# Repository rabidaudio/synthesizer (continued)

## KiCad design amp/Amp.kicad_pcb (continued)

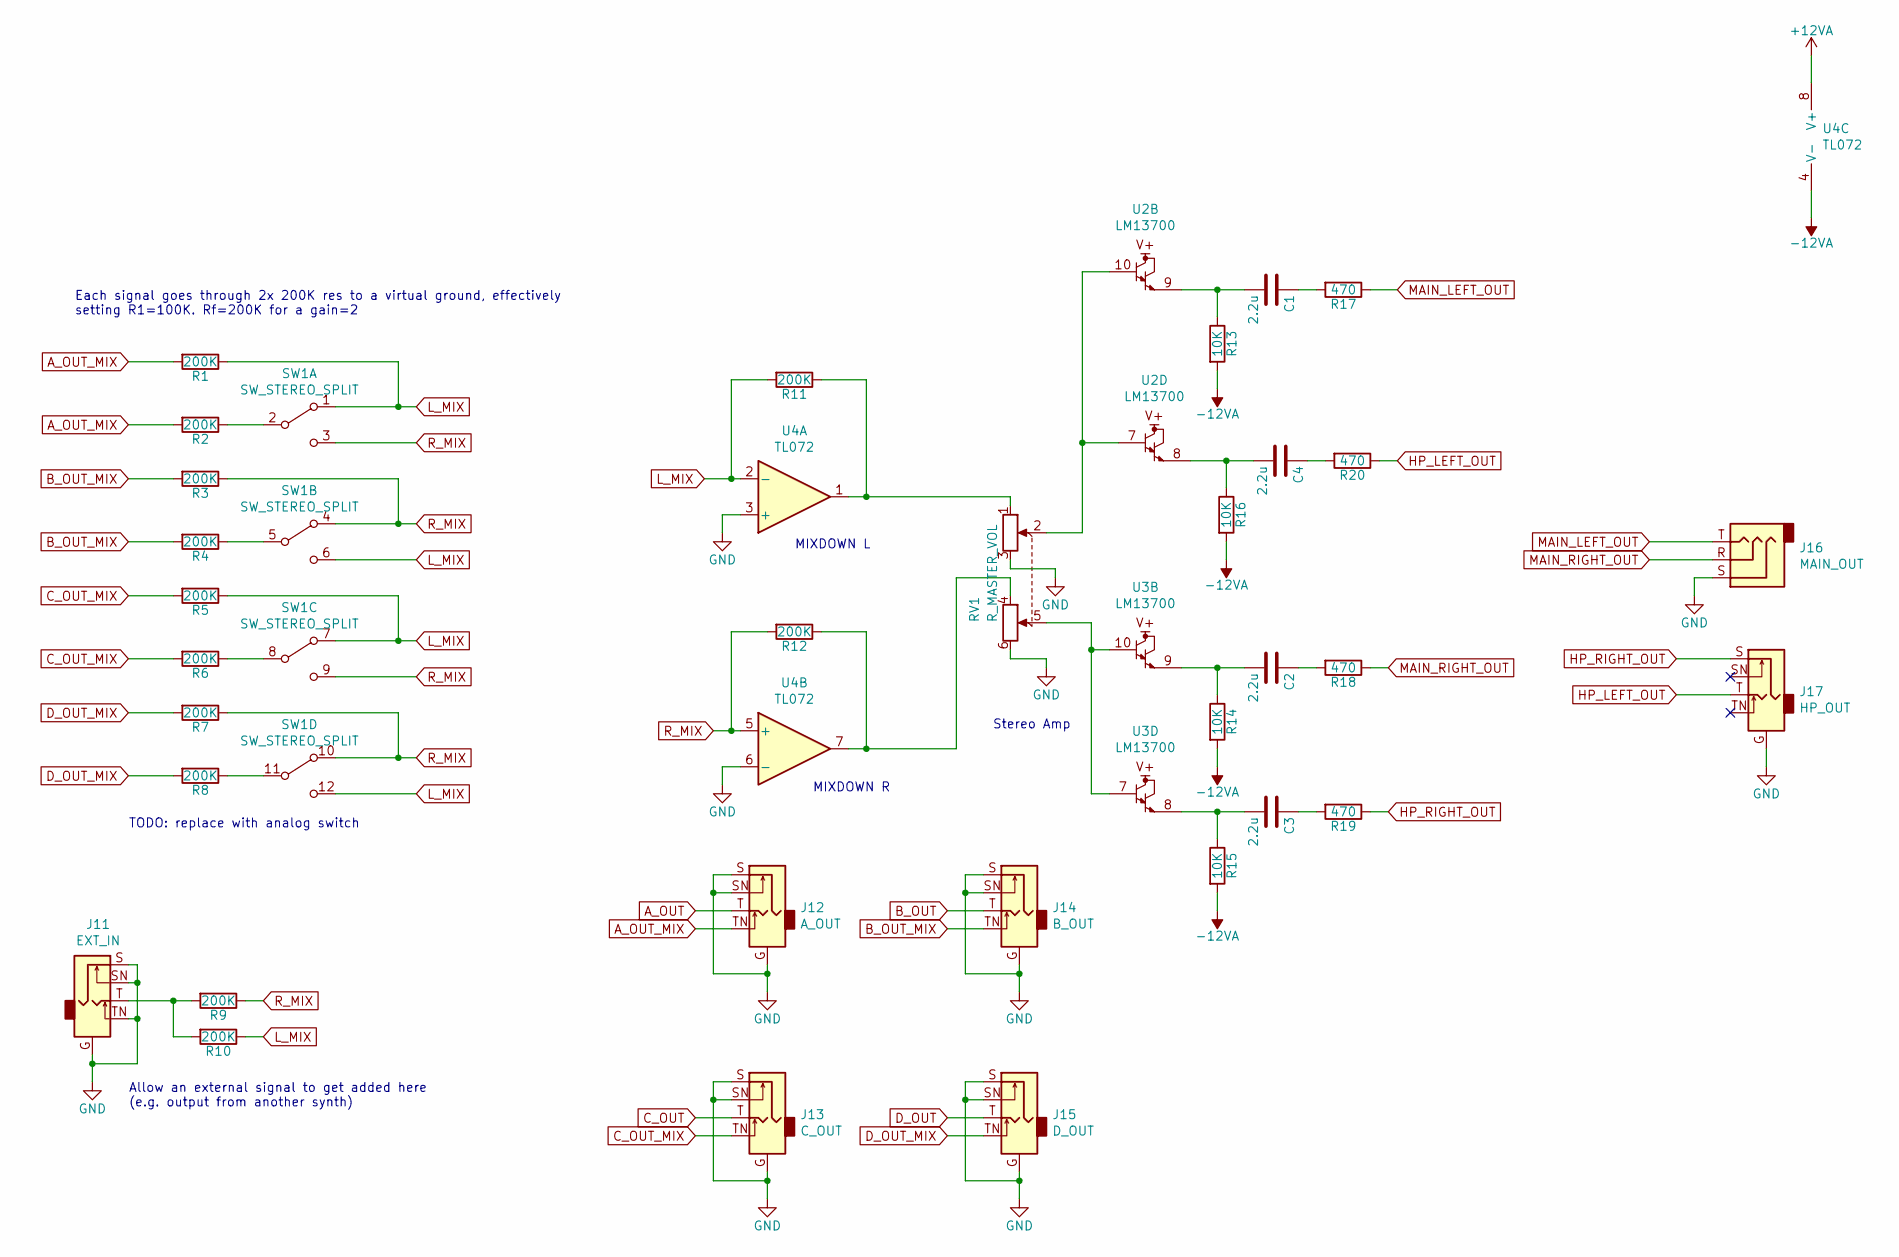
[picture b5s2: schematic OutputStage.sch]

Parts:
C1, C2, C3, C4: 2.2u; C_Radial_D6.3mm_H5.0mm_P2.50mm
J11: EXT_IN; 3.5MM_Jack_Breakout_Vertical
J12: A_OUT; 3.5MM_Jack_Breakout_Vertical
J13: C_OUT; 3.5MM_Jack_Breakout_Vertical
J14: B_OUT; 3.5MM_Jack_Breakout_Vertical
J15: D_OUT; 3.5MM_Jack_Breakout_Vertical
J16: MAIN_OUT; PinHeader_1x03_P2.54mm_Vertical
J17: HP_OUT; 3.5MM_Jack_Breakout_Vertical
R1, R2, R3, R4, R5, R6, R7, R8, R9, R10, R11, R12: 200K; R_Axial_DIN0204_L3.6mm_D1.6mm_P1.90mm_Vertical
R13, R14, R15, R16: 10K; R_Axial_DIN0204_L3.6mm_D1.6mm_P1.90mm_Vertical
R17, R18, R19, R20: 470; R_Axial_DIN0204_L3.6mm_D1.6mm_P1.90mm_Vertical
RV1: R_MASTER_VOL; PinHeader_2x03_P2.54mm_Vertical
SW1: SW_STEREO_SPLIT; PinHeader_2x06_P2.54mm_Vertical
U2, U3: LM13700; DIP-16_W7.62mm
U4: TL072; DIP-8_W7.62mm

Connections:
+12VA: U4.8 (V+); also elsewhere on the board
-12VA: R13.2, R14.2, R15.2, R16.2, U4.4 (V-); also elsewhere on the board
A_OUT: J12.T; also elsewhere on the board
A_OUT_MIX: J12.TN, R1.2, R2.2
B_OUT: J14.T; also elsewhere on the board
B_OUT_MIX: J14.TN, R3.2, R4.2
C_OUT: J13.T; also elsewhere on the board
C_OUT_MIX: J13.TN, R5.2, R6.2
D_OUT: J15.T; also elsewhere on the board
D_OUT_MIX: J15.TN, R7.2, R8.2
GND: J11.G, J11.S, J11.SN, J11.TN, J12.G, J12.S, J12.SN, J13.G, J13.S, J13.SN, J14.G, J14.S, J14.SN, J15.G, J15.S, J15.SN, J16.S, J17.G, RV1.3, RV1.6, U2.4 (-), U3.4 (-), U4.3 (+), U4.6 (-); also elsewhere on the board
HP_LEFT_OUT: J17.T, R20.1
HP_RIGHT_OUT: J17.S, R19.1
L_MIX: R1.1, R5.1, R10.1, R11.2, SW1.1 (A), SW1.6 (C), SW1.7 (A), SW1.12 (C), U4.2 (-)
MAIN_LEFT_OUT: J16.T, R17.1
MAIN_RIGHT_OUT: J16.R, R18.1
unnamed: C1.1, R17.2
unnamed: C1.2, R13.1, U2.9
unnamed: C2.1, R18.2
unnamed: C2.2, R14.1, U3.9
unnamed: C3.1, R19.2
unnamed: C3.2, R15.1, U3.8
unnamed: C4.1, R20.2
unnamed: C4.2, R16.1, U2.8
unnamed: J11.T, R9.2, R10.2
unnamed 60: U3.1; also elsewhere on the board
unnamed 63: U2.1; also elsewhere on the board
unnamed: R2.1, SW1.2 (B)
unnamed: R4.1, SW1.5 (B)
unnamed: R6.1, SW1.8 (B)
unnamed: R8.1, SW1.11 (B)
unnamed: R11.1, RV1.1, U4.1
unnamed: R12.1, RV1.4, U4.7
unnamed 91: U3.3 (+); also elsewhere on the board
unnamed 94: U3.5; also elsewhere on the board
unnamed 99: U2.3 (+); also elsewhere on the board
unnamed 102: U2.5; also elsewhere on the board
unnamed: RV1.2, U2.7, U2.10
unnamed: RV1.5, U3.7, U3.10
R_MIX: R3.1, R7.1, R9.1, R12.2, SW1.3 (C), SW1.4 (A), SW1.9 (C), SW1.10 (A), U4.5 (+)

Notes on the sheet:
Stereo Amp
Each signal goes through 2x 200K res to a virtual ground, effectively setting R1=100K. Rf=200K for a gain=2
MIXDOWN L
MIXDOWN R
Allow an external signal to get added here (e.g. output from another synth)
TODO: replace with analog switch

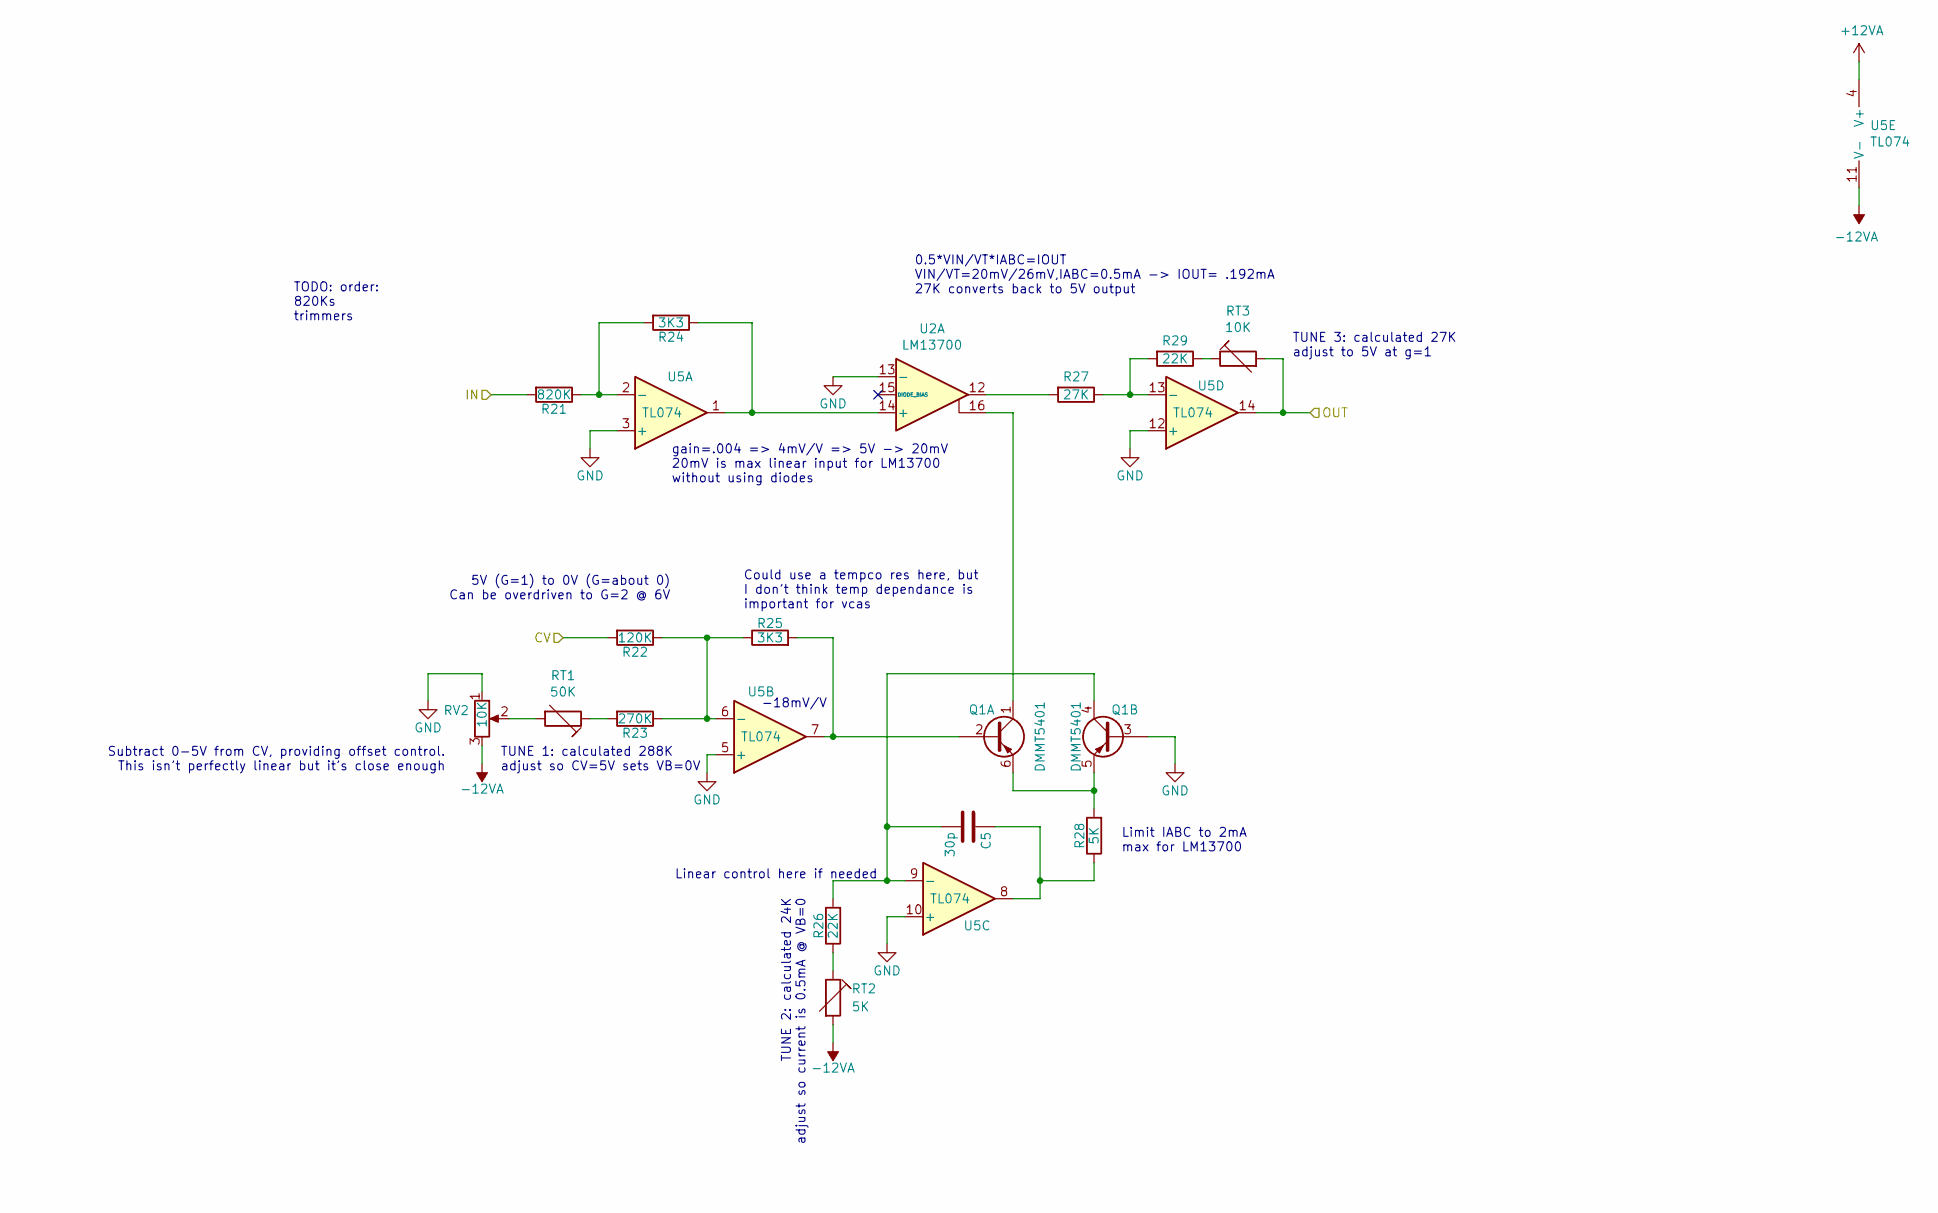
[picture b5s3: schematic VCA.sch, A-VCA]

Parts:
C5: 30p; C_Disc_D3.0mm_W2.0mm_P2.50mm
Q1: DMMT5401; SOT-23-6
R21: 820K; R_Axial_DIN0204_L3.6mm_D1.6mm_P1.90mm_Vertical
R22: 120K; R_Axial_DIN0204_L3.6mm_D1.6mm_P1.90mm_Vertical
R23: 270K; R_Axial_DIN0204_L3.6mm_D1.6mm_P1.90mm_Vertical
R24, R25: 3K3; R_Axial_DIN0204_L3.6mm_D1.6mm_P1.90mm_Vertical
R26, R29: 22K; R_Axial_DIN0204_L3.6mm_D1.6mm_P1.90mm_Vertical
R27: 27K; R_Axial_DIN0204_L3.6mm_D1.6mm_P1.90mm_Vertical
R28: 5K; R_Axial_DIN0204_L3.6mm_D1.6mm_P1.90mm_Vertical
RT1: 50K; R_Box_L14.0mm_W5.0mm_P9.00mm
RT2: 5K; R_Box_L14.0mm_W5.0mm_P9.00mm
RT3: 10K; R_Box_L14.0mm_W5.0mm_P9.00mm
RV2: 10K; slide_potentiometer_35mm
U2: LM13700; DIP-16_W7.62mm
U5: TL074; DIP-14_W7.62mm

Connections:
+12VA: U5.4 (V+); also elsewhere on the board
-12VA: RT2.2, RV2.3, U5.11 (V-); also elsewhere on the board
A_CV: R22.2; also elsewhere on the board
A_IN: R21.2; also elsewhere on the board
A_OUT: RT3.2, U5.14; also elsewhere on the board
GND: Q1.3 (B2), RV2.1, U2.4 (-), U2.13 (-), U5.3 (+), U5.5 (+), U5.10 (+), U5.12 (+); also elsewhere on the board
unnamed: C5.1, R28.1, U5.8
unnamed: C5.2, Q1.4 (C2), R26.2, U5.9 (-)
unnamed: Q1.1 (C1), U2.16
unnamed: Q1.2 (B1), R25.2, U5.7
unnamed: Q1.5 (E2), Q1.6 (E1), R28.2
unnamed 63: U2.1; also elsewhere on the board
unnamed: R21.1, R24.2, U5.2 (-)
unnamed: R22.1, R23.1, R25.1, U5.6 (-)
unnamed: R23.2, RT1.1
unnamed: R24.1, U2.14 (+), U5.1
unnamed: R26.1, RT2.1
unnamed: R27.1, R29.2, U5.13 (-)
unnamed: R27.2, U2.12
unnamed: R29.1, RT3.1
unnamed 99: U2.3 (+); also elsewhere on the board
unnamed 102: U2.5; also elsewhere on the board
unnamed: RT1.2, RV2.2

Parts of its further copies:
C6, C7, C8: 30p; C_Disc_D3.0mm_W2.0mm_P2.50mm
Q2, Q3, Q4: DMMT5401; SOT-23-6
R30, R39, R48: 820K; R_Axial_DIN0204_L3.6mm_D1.6mm_P1.90mm_Vertical
R31, R40, R49: 120K; R_Axial_DIN0204_L3.6mm_D1.6mm_P1.90mm_Vertical
R32, R41, R50: 270K; R_Axial_DIN0204_L3.6mm_D1.6mm_P1.90mm_Vertical
R33, R34, R42, R43, R51, R52: 3K3; R_Axial_DIN0204_L3.6mm_D1.6mm_P1.90mm_Vertical
R35, R38, R44, R47, R53, R56: 22K; R_Axial_DIN0204_L3.6mm_D1.6mm_P1.90mm_Vertical
R36, R45, R54: 27K; R_Axial_DIN0204_L3.6mm_D1.6mm_P1.90mm_Vertical
R37, R46, R55: 5K; R_Axial_DIN0204_L3.6mm_D1.6mm_P1.90mm_Vertical
RT4, RT7, RT10: 50K; R_Box_L14.0mm_W5.0mm_P9.00mm
RT5, RT8, RT11: 5K; R_Box_L14.0mm_W5.0mm_P9.00mm
RT6, RT9, RT12: 10K; R_Box_L14.0mm_W5.0mm_P9.00mm
RV3, RV4, RV5: 10K; slide_potentiometer_35mm
U6, U7, U8: TL074; DIP-14_W7.62mm

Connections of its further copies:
+12VA: U6.4 (V+), U7.4 (V+), U8.4 (V+); also elsewhere on the board
-12VA: RT5.2, RT8.2, RT11.2, RV3.3, RV4.3, RV5.3, U6.11 (V-), U7.11 (V-), U8.11 (V-); also elsewhere on the board
B_CV: R49.2; also elsewhere on the board
B_IN: R48.2; also elsewhere on the board
B_OUT: RT12.2, U8.14; also elsewhere on the board
C_CV: R31.2; also elsewhere on the board
C_IN: R30.2; also elsewhere on the board
C_OUT: RT6.2, U6.14; also elsewhere on the board
D_CV: R40.2; also elsewhere on the board
D_IN: R39.2; also elsewhere on the board
D_OUT: RT9.2, U7.14; also elsewhere on the board
GND: Q2.3 (B2), Q3.3 (B2), Q4.3 (B2), RV3.1, RV4.1, RV5.1, U6.3 (+), U6.5 (+), U6.10 (+), U6.12 (+), U7.3 (+), U7.5 (+), U7.10 (+), U7.12 (+), U8.3 (+), U8.5 (+), U8.10 (+), U8.12 (+); also elsewhere on the board
unnamed: C6.1, R37.1, U6.8
unnamed: C6.2, Q2.4 (C2), R35.2, U6.9 (-)
unnamed: C7.1, R46.1, U7.8
unnamed: C7.2, Q3.4 (C2), R44.2, U7.9 (-)
unnamed: C8.1, R55.1, U8.8
unnamed: C8.2, Q4.4 (C2), R53.2, U8.9 (-)
unnamed 57: Q2.1 (C1); also elsewhere on the board
unnamed: Q2.2 (B1), R34.2, U6.7
unnamed: Q2.5 (E2), Q2.6 (E1), R37.2
unnamed 60: Q3.1 (C1); also elsewhere on the board
unnamed: Q3.2 (B1), R43.2, U7.7
unnamed: Q3.5 (E2), Q3.6 (E1), R46.2
unnamed 63: Q4.1 (C1); also elsewhere on the board
unnamed: Q4.2 (B1), R52.2, U8.7
unnamed: Q4.5 (E2), Q4.6 (E1), R55.2
unnamed: R30.1, R33.2, U6.2 (-)
unnamed: R31.1, R32.1, R34.1, U6.6 (-)
unnamed: R32.2, RT4.1
unnamed 83: R33.1, U6.1; also elsewhere on the board
unnamed: R35.1, RT5.1
unnamed: R36.1, R38.2, U6.13 (-)
unnamed 86: R36.2; also elsewhere on the board
unnamed: R38.1, RT6.1
unnamed: R39.1, R42.2, U7.2 (-)
unnamed: R40.1, R41.1, R43.1, U7.6 (-)
unnamed: R41.2, RT7.1
unnamed 91: R42.1, U7.1; also elsewhere on the board
unnamed: R44.1, RT8.1
unnamed: R45.1, R47.2, U7.13 (-)
unnamed 94: R45.2; also elsewhere on the board
unnamed: R47.1, RT9.1
unnamed: R48.1, R51.2, U8.2 (-)
unnamed: R49.1, R50.1, R52.1, U8.6 (-)
unnamed: R50.2, RT10.1
unnamed 99: R51.1, U8.1; also elsewhere on the board
unnamed: R53.1, RT11.1
unnamed: R54.1, R56.2, U8.13 (-)
unnamed 102: R54.2; also elsewhere on the board
unnamed: R56.1, RT12.1
unnamed: RT4.2, RV3.2
unnamed: RT7.2, RV4.2
unnamed: RT10.2, RV5.2

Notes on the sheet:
5V (G=1) to 0V (G=about 0) Can be overdriven to G=2 @ 6V
Linear control here if needed
Subtract 0-5V from CV, providing offset control. This isn’t perfectly linear but it’s close enough
-18mV/V
TUNE 2: calculated 24K adjust so current is 0.5mA @ VB=0
Limit IABC to 2mA max for LM13700
gain=.004 => 4mV/V => 5V -> 20mV 20mV is max linear input for LM13700 without using diodes
0.5*VIN/VT*IABC=IOUT VIN/VT=20mV/26mV,IABC=0.5mA -> IOUT= .192mA 27K converts back to 5V output
TODO: order: 820Ks trimmers
Could use a tempco res here, but I don’t think temp dependance is important for vcas
TUNE 1: calculated 288K adjust so CV=5V sets VB=0V
TUNE 3: calculated 27K adjust to 5V at g=1

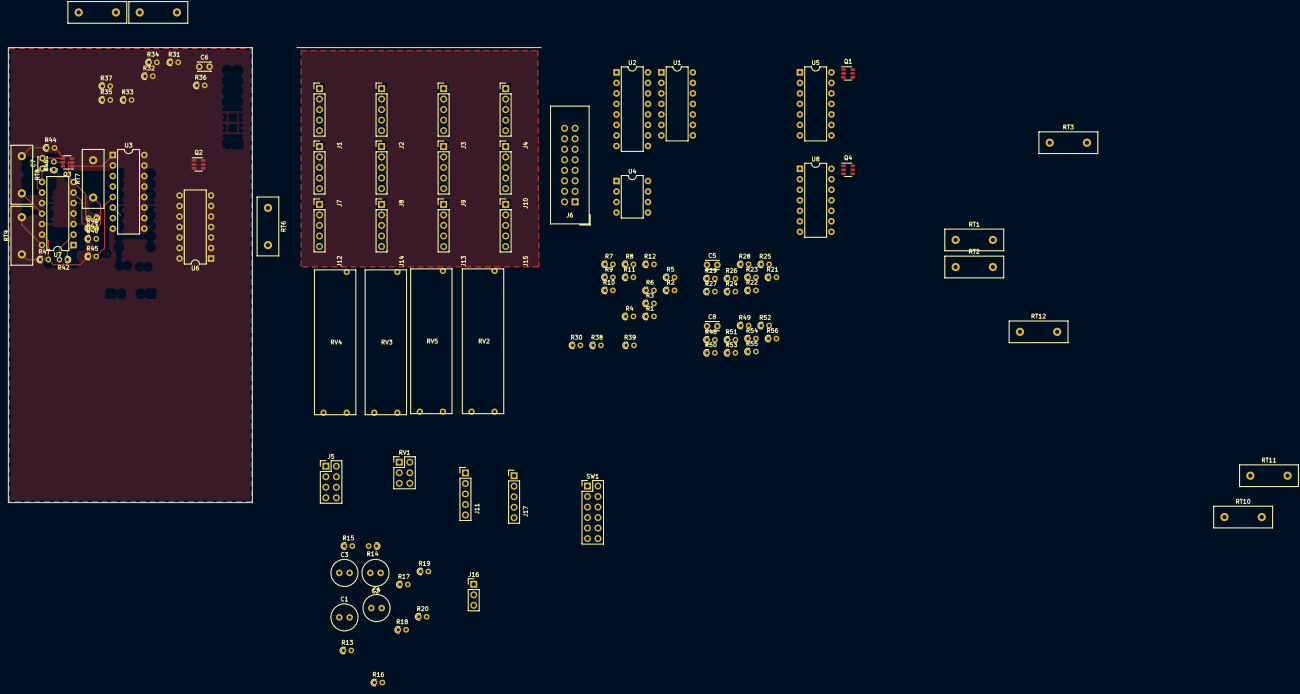
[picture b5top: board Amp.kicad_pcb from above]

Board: 2 copper layers, 128.8 x 110.0 mm, 111 parts (0 on the bottom side), 105 nets.

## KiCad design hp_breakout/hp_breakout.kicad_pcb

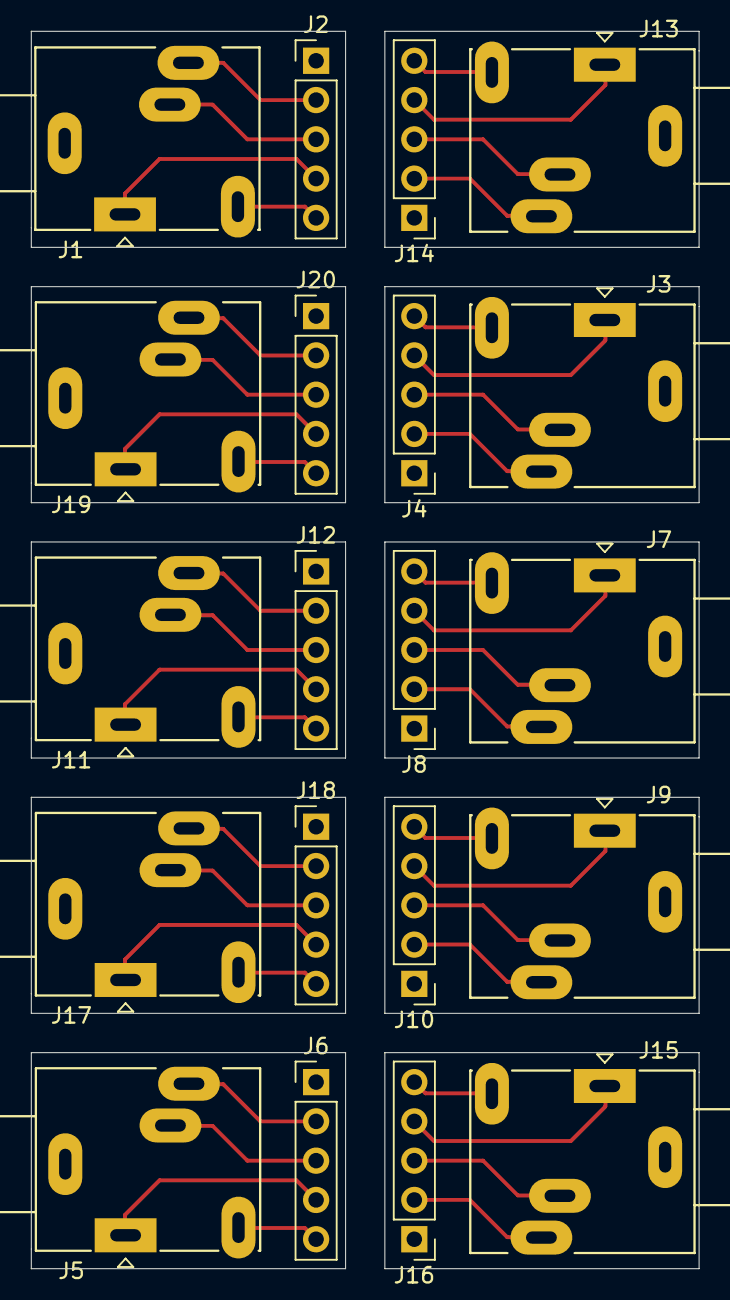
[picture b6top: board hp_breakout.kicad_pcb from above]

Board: 2 copper layers, 43.2 x 80.0 mm, 20 parts (0 on the bottom side), 50 nets.

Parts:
J1, J3, J5, J7, J9, J11, J13, J15, J17, J19: AudioJack2_Ground_Switch; Jack_3.5mm_Ledino_KB3SPRS_Horizontal
J2, J4, J6, J8, J10, J12, J14, J16, J18, J20: Conn_01x05_Male; PinHeader_1x05_P2.54mm_Vertical

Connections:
/U?/R: J1.R, J2.2
/U?/RN: J1.RN, J2.3
/U?/S: J1.S, J2.1
/U?/T: J1.T, J2.4
/U?/TN: J1.TN, J2.5
/sheet5E6F4A6A/R: J13.R, J14.2
/sheet5E6F4A6A/RN: J13.RN, J14.3
/sheet5E6F4A6A/S: J13.S, J14.1
/sheet5E6F4A6A/T: J13.T, J14.4
/sheet5E6F4A6A/TN: J13.TN, J14.5
/sheet5E6F4A6C/R: J15.R, J16.2
/sheet5E6F4A6C/RN: J15.RN, J16.3
/sheet5E6F4A6C/S: J15.S, J16.1
/sheet5E6F4A6C/T: J15.T, J16.4
/sheet5E6F4A6C/TN: J15.TN, J16.5
/sheet5E6F4A6E/R: J17.R, J18.2
/sheet5E6F4A6E/RN: J17.RN, J18.3
/sheet5E6F4A6E/S: J17.S, J18.1
/sheet5E6F4A6E/T: J17.T, J18.4
/sheet5E6F4A6E/TN: J17.TN, J18.5
/sheet5E6F4A68/R: J11.R, J12.2
/sheet5E6F4A68/RN: J11.RN, J12.3
/sheet5E6F4A68/S: J11.S, J12.1
/sheet5E6F4A68/T: J11.T, J12.4
/sheet5E6F4A68/TN: J11.TN, J12.5
/sheet5E6F4A70/R: J19.R, J20.2
/sheet5E6F4A70/RN: J19.RN, J20.3
/sheet5E6F4A70/S: J19.S, J20.1
/sheet5E6F4A70/T: J19.T, J20.4
/sheet5E6F4A70/TN: J19.TN, J20.5
/sheet5E6F46C9/R: J5.R, J6.2
/sheet5E6F46C9/RN: J5.RN, J6.3
/sheet5E6F46C9/S: J5.S, J6.1
/sheet5E6F46C9/T: J5.T, J6.4
/sheet5E6F46C9/TN: J5.TN, J6.5
/sheet5E6F46CB/R: J7.R, J8.2
/sheet5E6F46CB/RN: J7.RN, J8.3
/sheet5E6F46CB/S: J7.S, J8.1
/sheet5E6F46CB/T: J7.T, J8.4
/sheet5E6F46CB/TN: J7.TN, J8.5
/sheet5E6F47F3/R: J9.R, J10.2
/sheet5E6F47F3/RN: J9.RN, J10.3
/sheet5E6F47F3/S: J9.S, J10.1
/sheet5E6F47F3/T: J9.T, J10.4
/sheet5E6F47F3/TN: J9.TN, J10.5
/sheet5E6F4684/R: J3.R, J4.2
/sheet5E6F4684/RN: J3.RN, J4.3
/sheet5E6F4684/S: J3.S, J4.1
/sheet5E6F4684/T: J3.T, J4.4
/sheet5E6F4684/TN: J3.TN, J4.5

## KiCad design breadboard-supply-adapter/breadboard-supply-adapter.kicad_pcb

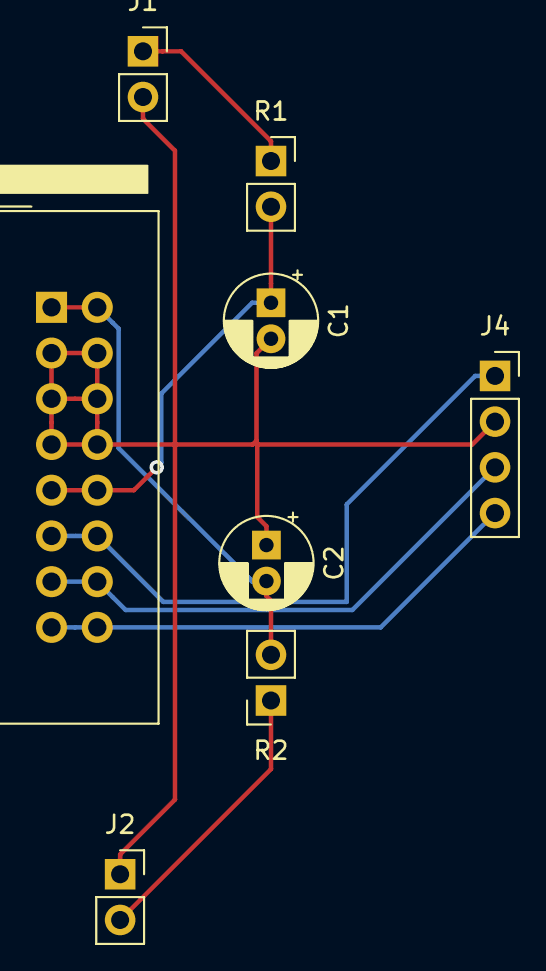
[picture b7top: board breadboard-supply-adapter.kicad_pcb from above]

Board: 2 copper layers, 8 parts (0 on the bottom side), 8 nets.

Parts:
C1, C2: CP; CP_Radial_D5.0mm_P2.00mm
J1, J2: Conn_01x02; PinSocket_1x02_P2.54mm_Vertical
J3: EURORACK_CONN_16_GATE_CV; EURORACK_16_IDC
J4: Conn_01x04; PinSocket_1x04_P2.54mm_Vertical
R1, R2: 0.5; PinSocket_1x02_P2.54mm_Vertical

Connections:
+12V: C1.1, J3.9, R1.2
-12V: C2.2, J3.1, R2.2
GND: C1.2, C2.1, J1.2, J2.1, J3.3, J4.2
unnamed: J1.1, R1.1
unnamed: J2.2, R2.1
unnamed: J3.11, J4.1
unnamed: J3.13, J4.3
unnamed: J3.15, J4.4

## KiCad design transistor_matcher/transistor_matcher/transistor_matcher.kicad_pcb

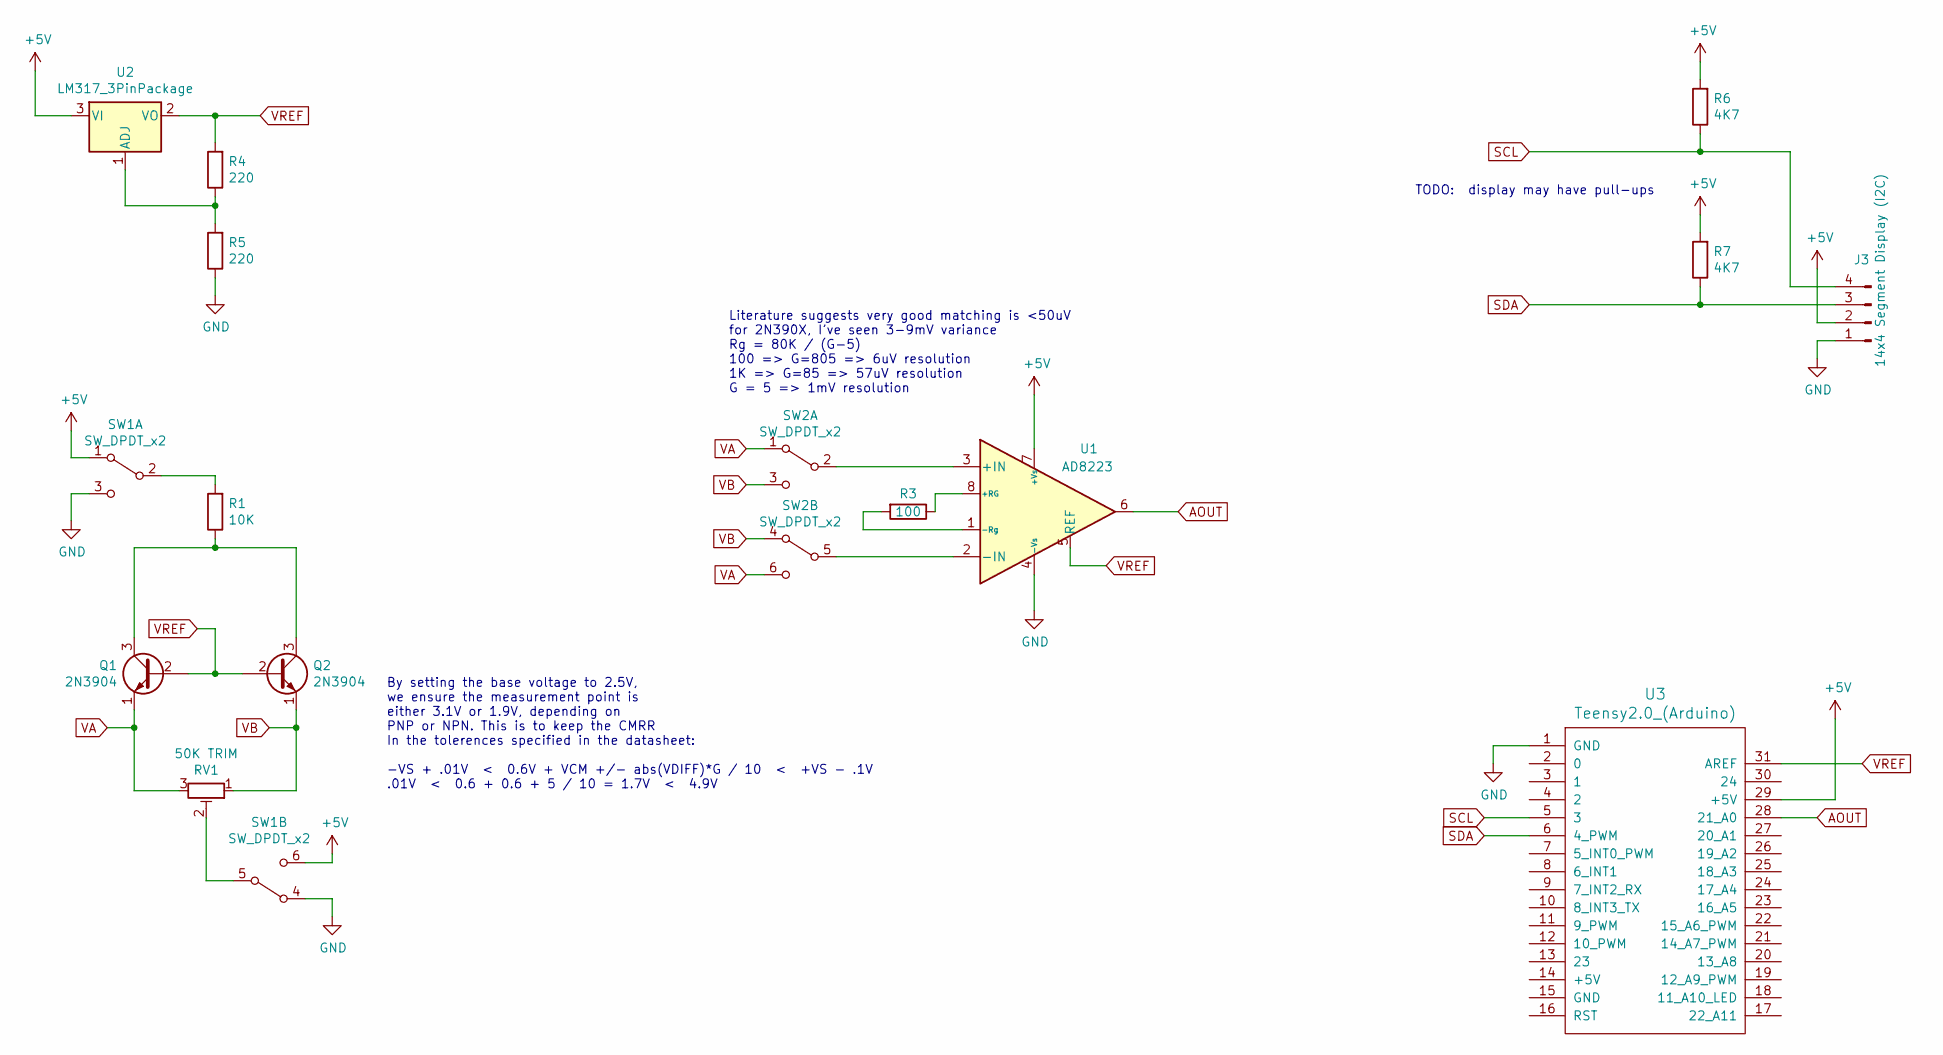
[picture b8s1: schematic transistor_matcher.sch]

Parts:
J3: 14x4 Segment Display (I2C); JST-4-PTH-VERT
Q1, Q2: 2N3904; BJT_Slot
R1: 10K; R_Axial_DIN0204_L3.6mm_D1.6mm_P1.90mm_Vertical
R3: 100; R_Axial_DIN0204_L3.6mm_D1.6mm_P1.90mm_Vertical
R4, R5: 220; R_Axial_DIN0204_L3.6mm_D1.6mm_P1.90mm_Vertical
R6, R7: 4K7; R_Axial_DIN0204_L3.6mm_D1.6mm_P1.90mm_Vertical
RV1: 50K TRIM; Potentiometer_Trimmer_Bourns_PV36W
SW1, SW2: SW_DPDT_x2; SW_E-Switch_EG1271_DPDT
U1: AD8223; SOIC-8_3.9x4.9mm_Pitch1.27mm
U2: LM317_3PinPackage; TO-220-3_Horizontal
U3: Teensy2.0_(Arduino); Teensy2.0

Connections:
+5V: J3.2, R6.2, R7.2, SW1.1 (A), SW1.6 (C), U1.7 (+Vs), U2.3 (VI), U3.29 (+5V)
AOUT: U1.6, U3.28 (21_A0)
GND: J3.1, R5.1, SW1.3 (C), SW1.4 (A), U1.4 (-Vs), U3.1 (GND)
unnamed: Q1.3 (C), Q2.3 (C), R1.1
unnamed: R1.2, SW1.2 (B)
unnamed: R3.1, U1.8 (+RG)
unnamed: R3.2, U1.1 (-Rg)
unnamed: R4.1, R5.2, U2.1 (ADJ)
unnamed: RV1.2, SW1.5 (B)
unnamed: SW2.2 (B), U1.3 (+IN)
unnamed: SW2.5 (B), U1.2 (-IN)
SCL: J3.4, R6.1, U3.5 (3)
SDA: J3.3, R7.1, U3.6 (4_PWM)
VA: Q1.1 (E), RV1.3, SW2.1 (A), SW2.6 (C)
VB: Q2.1 (E), RV1.1, SW2.3 (C), SW2.4 (A)
VREF: Q1.2 (B), Q2.2 (B), R4.2, U1.5 (REF), U2.2 (VO), U3.31 (AREF)

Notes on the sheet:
Literature suggests very good matching is <50uV for 2N390X, I’ve seen 3-9mV variance Rg = 80K / (G-5) 100 => G=805 => 6uV resolution 1K => G=85 => 57uV resolution G = 5 => 1mV resolution
By setting the base voltage to 2.5V, we ensure the measurement point is either 3.1V or 1.9V, depending on PNP or NPN. This is to keep the CMRR In the tolerences specified in the datasheet: -VS + .01V < 0.6V + VCM +/- abs(VDIFF)*G / 10 < +VS - .1V .01V < 0.6 + 0.6 + 5 / 10 = 1.7V < 4.9V
TODO: display may have pull-ups

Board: 2 copper layers, 15 parts (4 on the bottom side), 16 nets, no tracks yet.

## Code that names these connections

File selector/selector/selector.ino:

/** Configuration **/
// which pin to read from
const int analogPin = A1;
// number of bins
const int binCount = 4;
// which digital output pins to use for each bin
const int binPins[binCount] = { 0, 1, 3, 4 };
// the percent beyond the cutoff you must turn for a change to occur
const float hysteresis = 0.05;
#define DEBUG false

// it would be more efficient to use ints instead of floats but
// performance isn't really a concern here and it means we can
// easily support arbitrary configurations
const float binSize = 1024 / (float) binCount;
const float overlap = hysteresis * binSize;
size_t state = -1;

void setup() {
  for (size_t i = 0; i < binCount; i++) {
    pinMode(binPins[i], OUTPUT);
    digitalWrite(binPins[i], LOW);
  }
//  if (DEBUG) {
//    Serial.begin(9600);
//    Serial.print("binSize: "); Serial.println(binSize);
//    Serial.print("overlap: "); Serial.println(overlap);
//  }
}

void loop() {
  float value = (float) analogRead(analogPin);
//    if (DEBUG) {
//      Serial.print("value: "); Serial.println(value);
//    }
  float upperBound = ((state + 1) * binSize) + overlap;
  float lowerBound = (state * binSize) - overlap;
  if (value > upperBound) {
    setState(state + 1);
  } else if (value < lowerBound) {
    setState(state - 1);
  }
}

void setState(size_t s) {
  if (s == state) return;
  digitalWrite(binPins[state], LOW);
  digitalWrite(binPins[s], HIGH);
  state = s;
//  if (DEBUG) {
//    Serial.print("state: "); Serial.println(state);
//  }
}

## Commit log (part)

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2015-04-28 inital commit
2015-05-04 new stuff
2015-05-05 cleaned up
2015-05-05 added classwork
2015-05-05 added textbook
2015-05-05 added ADC, cleaned up schematic
2015-05-05 added osc for seq
2015-05-13 uncommited board changes
2015-05-15 started preso work
2015-05-17 the new sequencer kicks so much ass
2015-05-17 better comments
2015-05-17 updated sequencer eagle files for current version
2015-05-17 updated schematic for BOM
2015-05-20 board tweaks
2015-05-20 added pdf rendering stuff
2015-05-20 basic webcam stuff
2015-05-20 uggh i should have started this hours ago
2015-05-20 uggh
2015-05-20 fuck me
2015-05-20 might just make it
2015-05-20 fuckitshipit
2015-05-20 fingers crossed
2016-07-17 added other files
2019-04-11 started amplifier design
2019-04-15 getting close on the amp
2019-05-28 updated amp - LM13700 with PNP-exp. control
2020-03-15 created base connector breakout project
2020-03-15 10 identical boards
2020-03-15 update amp to kicad 5
2020-03-16 updated amp schematic with glue
2020-03-17 updated VCA based on new calculations
2020-03-17 added notes
2020-03-20 started transistor_matcher circuit
2020-03-20 updated schematic for VBE measurement, started on board layout
2020-03-21 simplfied based on emperical tests
2020-03-28 basic sketch to prove inst. amp is working I think we really need a constant upper reference voltage
2020-03-29 updated to include display
2020-04-05 got working amplifier
2020-04-05 separated amp into sheets
2020-05-03 updated notes
2020-05-20 reworked amp sheets and notes
2020-05-20 update amp config for quad-cascade design
2020-05-20 add eurorack connector, fix some issues
2020-05-21 initial vco notes (not thoroughly validated or calculated
2020-05-21 ltspice sim for lm13700 square/triangle vco
2020-05-23 rename shared kicad dir
2020-05-23 created utility module
2020-05-23 fix for eurorack connector
2020-05-23 added a few more untility footprints
2020-05-24 use jacks directly for horizontal
2020-05-24 switched fet with cd4066
2020-05-24 pcb mostly laid out
2020-05-24 cleanup
2020-05-24 shrunk board
2020-05-24 move the quirks of the pcb out of the schematic
2020-05-24 switch to 10-pin header
2020-05-24 use +/-10V power supply for amps
2020-05-24 reconnect 4066 headers
2020-05-25 LED driver for gate
2020-05-25 experimented some more with the led
2020-05-25 quick prototype of a breadboard power supply connector
2020-05-25 reversed the polarity of the neg cap (oops)
2020-05-28 rework PCB
2020-05-28 shrunk board significantly
2020-05-28 use through-holes for pot
2020-05-30 cleanup repo
2020-05-30 planning pannel layout
2020-05-30 testing 555 as pwm control
2020-05-30 add support for fixed CV output when no input
2020-05-30 correction based on breadboard test
2020-05-31 lots of panel design work
2020-05-31 correct ground issue
2020-05-31 move duplicate directory
2020-06-01 made progress on VCO
2020-06-02 fix some bugs in the circuit
2020-06-02 update graphics based on measurements
2020-06-02 fix amp connector
2020-06-06 it oscilates!
2020-06-06 vco planning
2020-06-06 output selector CV
2020-06-07 started vac layout
2020-06-07 more vca layout
2020-06-08 update amp
2020-06-08 working spice simulation
2020-06-08 added calculations
2020-06-08 adjust params to lower gain=1 current to keep shape up to gain=2
2020-06-08 updated schematic to match
2020-06-08 documented amplifier
2020-06-09 documented utils
2020-06-16 updated vco calculations
2020-06-16 experimenting with error
2020-06-17 add notes from test assembly
2020-07-04 reworked utilities around better analog switch modules
2020-07-04 restarted pcb
2020-07-04 reworked silkscreen
2020-07-04 corrected pin order on the pot breakout
2020-07-05 update components
2020-07-20 started envelope design
2020-07-20 tested utils rev b
2020-08-01 got analog latch working, started schematic
2020-08-01 component selection
2020-08-01 prepared pcb for dual envelopes
2020-08-01 cleanup amp
2020-08-01 clean up documentation
2020-08-01 fix indents
2020-08-02 remove outdated notes
2020-08-02 get rid of propigating controls
2020-08-02 adjusted amp to a 10V control voltage range
2020-08-02 scaled adsr to support 0-10V input
2020-08-02 use a current mirror to isolate reference currents, buffer vin, tune params
2020-08-02 use diode to force positive VIN
2020-08-02 update notes
2020-08-02 more accurate notes about lm13700
2020-08-02 notes
2020-08-03 add max simulation of transfer functions
2020-08-29 corrections based on prototype pcb
2020-08-31 output stage
2020-09-08 vco adjustments
2020-09-12 adjust waveshaper for 12V
2020-09-12 assembled breadboard VCO and waveshaper
2020-09-13 midi poc
2020-12-31 Update README.md
    add note about arp
2021-01-02 unsaved midi changes
2021-01-02 vco notes
2021-01-03 write code for shape selector, design CV input stage of vco
2021-07-07 trying 555 as square wave converter of osc core
2021-09-07 util tweaks
2021-09-11 add vactrol datasheets
2021-09-13 rework ASDR
2021-09-14 more layout
2021-09-14 reduce to one input
2021-09-21 layout
2022-02-06 adsr improvements
2022-09-10 planning and proof-of-concept code
2022-09-10 set up platformio
2022-09-10 refactor code
2022-09-11 switch to attiny84 and think more about control scheme
2022-09-12 add swing support
2022-09-14 basic control mechanism
2022-09-14 improve display
2022-09-14 implement tap tempo
2022-09-15 convert pot to rotary switch
2022-09-15 connect interface to rotary switch
2022-09-19 move reference to blog
2022-09-24 rework clock circuit
2022-09-24 proof-of-concept LED driver
2022-09-24 re-integrate new display with main code
2022-09-25 pcb layout first pass
2022-09-25 cleanup pcb and silkscreen
2022-10-08 additional cleanup
2022-10-08 switch to frequency correct mode and update bpm register values
2022-10-08 CV tempo control
2022-10-08 analog input pin protection
2022-10-16 refactor
2022-10-16 tuned
2022-10-16 reimport backpack code and make def switch for it
2022-10-16 set up code for bare uno option
2022-10-16 get working on bare mcu
2022-10-17 update pcb
2022-10-17 switch side of bottom header for structural support
2022-10-17 simplify some complex routing
2022-11-25 redesign pcb around rotary encoder
2022-11-25 make a bit more space
2023-01-01 testing rotary encoder
2023-01-01 working encoder
2023-01-01 verified hardware
2023-01-01 fix PCB
2023-01-01 beautify schematic
2023-01-02 update to Kicad 6 and fix some layout issues
2023-01-02 update adsr to kicad 6
2023-01-02 re-annotate schematic
2023-01-08 create panel for clock module
2023-01-21 fix 7-segment displays
2023-01-21 fix some PCB bugs
2023-01-21 fix inputs
2023-01-22 pause support
2023-01-31 re-create panel in kicad
2023-02-03 graphics
2023-02-14 updated layout
2023-02-20 updated panel
2023-02-27 new spooky designs
2023-02-27 test out on pcb
2023-03-05 import panel designs and assets
2023-03-05 updated component appearances
2023-03-05 minor adjustments for component bounds
2023-03-05 import alternate design
2023-03-06 make ground plane connected, move LEDs wide
2023-03-06 back graphics
2023-03-07 rendered main design
2023-03-07 added panel to pcb
2023-03-07 render alternate design
2023-03-07 render gerbers
2023-03-18 move logos to soldermask
2023-03-18 fix design issues
2023-03-18 subdivisions both ways
2023-03-18 flip display direction of subdivisions
2023-03-19 add support for saving and loading settings
2023-03-19 display the base value when changing, else true value
2023-03-19 refactor displays to abstract class
2023-04-30 fix swing
2023-04-30 adust resolution of swing to be in %
2023-04-30 rework menu setup
2023-04-30 fix bug in timer
2023-04-30 expand range
2023-04-30 cleanup readme
2023-05-01 increase crystal footprint
2023-05-01 generate rev b gerbers
2023-05-01 cleanup old files
2023-05-01 fixed and separated pcb
2024-10-22 add reusable openscad layout definitions
2024-10-22 create script for extracting center points from openscad dxf
2024-10-23 cleanup synth shared footprints
2024-10-23 flip y orientation
2024-10-23 reverse y-axis orientation
2024-10-23 Revert "reverse y-axis orientation"
    This reverts commit be2b3902423d8e89fe58d89905e9280b5649029d.
2024-10-23 Revert "flip y orientation"
    This reverts commit a8479f8d3d33ab95d629eb13d20a0d69ed88b72e.
2024-10-23 add reverse flag
2024-11-24 keepouts and courtyards for screw components
2024-11-24 fix keepouts
2025-12-01 Bump fonttools from 4.54.1 to 4.61.0 in /shared/extract_dxf_centers
    Bumps [fonttools](https://github.com/fonttools/fonttools) from 4.54.1 to 4.61.0.
    - [Release notes](https://github.com/fonttools/fonttools/releases)
    - [Changelog](https://github.com/fonttools/fonttools/blob/main/NEWS.rst)
    - [Commits](https://github.com/fonttools/fonttools/compare/4.54.1...4.61.0)
    ---
    updated-dependencies:
2025-12-16 Bump filelock from 3.16.1 to 3.20.1 in /shared/extract_dxf_centers
    Bumps [filelock](https://github.com/tox-dev/py-filelock) from 3.16.1 to 3.20.1.
    - [Release notes](https://github.com/tox-dev/py-filelock/releases)
    - [Changelog](https://github.com/tox-dev/filelock/blob/main/docs/changelog.rst)
    - [Commits](https://github.com/tox-dev/py-filelock/compare/3.16.1...3.20.1)
    ---
    updated-dependencies:
2026-01-13 Bump virtualenv from 20.27.0 to 20.36.1 in /shared/extract_dxf_centers
    Bumps [virtualenv](https://github.com/pypa/virtualenv) from 20.27.0 to 20.36.1.
    - [Release notes](https://github.com/pypa/virtualenv/releases)
    - [Changelog](https://github.com/pypa/virtualenv/blob/main/docs/changelog.rst)
    - [Commits](https://github.com/pypa/virtualenv/compare/20.27.0...20.36.1)
    ---
    updated-dependencies:
2026-01-13 Bump filelock from 3.16.1 to 3.20.3 in /shared/extract_dxf_centers
    Bumps [filelock](https://github.com/tox-dev/py-filelock) from 3.16.1 to 3.20.3.
    - [Release notes](https://github.com/tox-dev/py-filelock/releases)
    - [Changelog](https://github.com/tox-dev/filelock/blob/main/docs/changelog.rst)
    - [Commits](https://github.com/tox-dev/py-filelock/compare/3.16.1...3.20.3)
    ---
    updated-dependencies:
